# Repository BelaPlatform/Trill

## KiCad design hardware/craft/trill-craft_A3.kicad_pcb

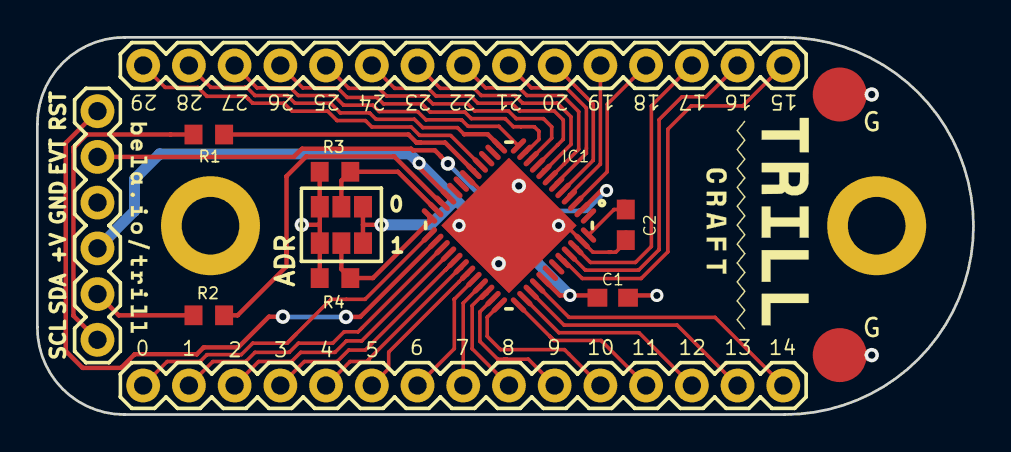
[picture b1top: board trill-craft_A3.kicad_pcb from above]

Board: 2 copper layers, 52.0 x 21.0 mm, 14 parts (0 on the bottom side), 41 nets.

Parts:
C1, C2: C-USC0603; C0603
G: Conn_01x01_Female; Circular_pad_smd
G#2: Conn_01x01_Female; Circular_pad_smd
IC1: CY8C206X6A; QFN48-LEADS
JP1: M06SILK_FEMALE_PTH; 1X06
JP3, JP4: Conn_01x15_Female; 1X15
Jumper0, Jumper1: Conn_01x03_Female; DOUBLE_SOLDER_JUMPER
R1, R2, R3, R4: R-EU_R0603; R0603

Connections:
/EVENT: IC1.2, JP1.2
/I2C_SCL: JP1.6, R1.2
/I2C_SDA: JP1.5, R2.2
/XRES: IC1.26, JP1.1
GND: C1.1, C2.2, G.1, G#2.1, IC1.18, IC1.47, IC1.EXP, JP1.3, Jumper0.3, Jumper1.3, R3.2, R4.2
unnamed: C2.1, IC1.48
unnamed: IC1.3, JP3.4
unnamed: IC1.4, JP3.5
unnamed: IC1.5, JP3.6
unnamed: IC1.6, JP3.7
unnamed: IC1.7, JP3.8
unnamed: IC1.8, JP3.9
unnamed: IC1.9, JP3.10
unnamed: IC1.10, JP3.11
unnamed: IC1.11, JP3.12
unnamed: IC1.12, JP3.13
unnamed: IC1.13, JP3.14
unnamed: IC1.16, JP3.15
unnamed: IC1.17, R1.1
unnamed: IC1.22, R2.1
unnamed: IC1.23, Jumper0.2, R3.1
unnamed: IC1.24, Jumper1.2, R4.1
unnamed: IC1.25, JP4.1
unnamed: IC1.27, JP4.2
unnamed: IC1.28, JP4.3
unnamed: IC1.29, JP4.4
unnamed: IC1.30, JP4.5
unnamed: IC1.31, JP4.6
unnamed: IC1.32, JP4.7
unnamed: IC1.33, JP4.8
unnamed: IC1.34, JP4.9
unnamed: IC1.35, JP4.10
unnamed: IC1.36, JP4.11
unnamed: IC1.37, JP4.12
unnamed: IC1.38, JP4.13
unnamed: IC1.39, JP4.14
unnamed: IC1.40, JP4.15
unnamed: IC1.44, JP3.1
unnamed: IC1.45, JP3.2
unnamed: IC1.46, JP3.3
VCC: C1.2, IC1.21, IC1.41, JP1.4, Jumper0.1, Jumper1.1

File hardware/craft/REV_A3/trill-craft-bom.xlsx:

Name | Quantity | Value | Package | Description | Mouser # | Digi-Key # | Datasheet / Notes
C1 | 1 | 0.1uF | "0603" | Capacitor ceramic 0402; standard bypass cap 5V+
C2 | 1 | 2.2nF | "0603" | Capacitor ceramic 0402; 5% | 81-GRM36X222J50
IC1 | 1 | CY8C20636A-24LTXI | 48-QFN, 7x7mm | IC Cypress SoC | 727-CY8C20636A24LTXI
R1-R2 | 2 | 100 ohm | "0603" | Resistor 0603 (standard part)
R3-R4 | 2 | 47k ohm | "0603" | Resistor 0603 (standard part)
Total | 7

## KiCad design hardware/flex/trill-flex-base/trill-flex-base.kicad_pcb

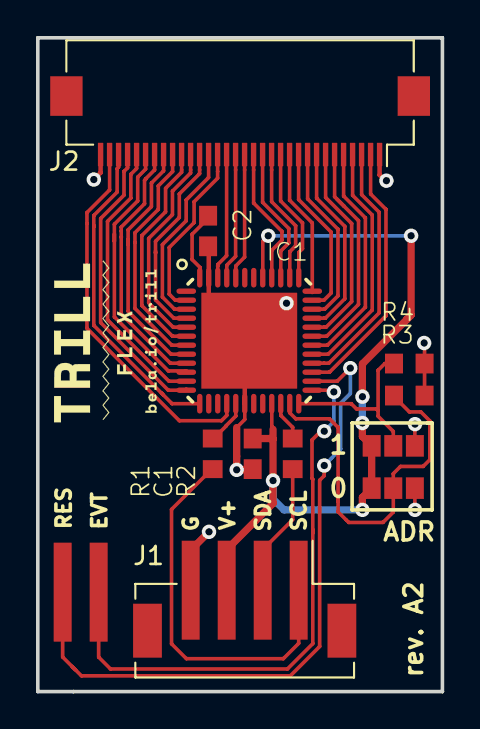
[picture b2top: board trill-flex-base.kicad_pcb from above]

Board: 2 copper layers, 22.5 x 36.3 mm, 12 parts (0 on the bottom side), 41 nets.

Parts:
C1, C2: C-USC0603; C0603
IC1: CY8C206X6A; QFN48-LEADS
J1: Conn_01x04_Female; JST_PH_B4B-PH-SM4-TB_04x2.00mm_Straight
J2: Conn_01x32; Hirose_FH12-32S-0.5SH_1x32-1MP_P0.50mm_Horizontal
J3: Conn_01x02_Female; JST_PH02x2.00mm_only_pins
Jumper0, Jumper1: Conn_01x03_Female; DOUBLE_SOLDER_JUMPER
R1, R2, R3, R4: R-EU_R0603; R0603

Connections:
/EVENT: IC1.25, J3.2
/I2C_SCL: J1.1, R1.2
/I2C_SDA: J1.2, R2.2
/SENSE1: IC1.27, J2.2
/SENSE2: IC1.28, J2.3
/SENSE3: IC1.29, J2.4
/SENSE4: IC1.30, J2.5
/SENSE5: IC1.31, J2.6
/SENSE6: IC1.32, J2.7
/SENSE7: IC1.33, J2.8
/SENSE8: IC1.34, J2.9
/SENSE9: IC1.35, J2.10
/SENSE10: IC1.36, J2.11
/SENSE11: IC1.37, J2.12
/SENSE12: IC1.38, J2.13
/SENSE13: IC1.39, J2.14
/SENSE14: IC1.40, J2.15
/SENSE15: IC1.44, J2.16
/SENSE16: IC1.45, J2.17
/SENSE17: IC1.46, J2.18
/SENSE18: IC1.2, J2.19
/SENSE19: IC1.3, J2.20
/SENSE20: IC1.4, J2.21
/SENSE21: IC1.5, J2.22
/SENSE22: IC1.6, J2.23
/SENSE23: IC1.7, J2.24
/SENSE24: IC1.8, J2.25
/SENSE25: IC1.9, J2.26
/SENSE26: IC1.10, J2.27
/SENSE27: IC1.11, J2.28
/SENSE28: IC1.12, J2.29
/SENSE29: IC1.13, J2.30
/SENSE30: IC1.16, J2.31
/XRES: IC1.26, J3.1
GND: C1.1, C2.2, IC1.18, IC1.47, IC1.EXP, J1.4, J2.1, J2.32, Jumper0.3, Jumper1.3, R3.2, R4.2
unnamed: C2.1, IC1.48
unnamed: IC1.17, R1.1
unnamed: IC1.22, R2.1
unnamed: IC1.23, Jumper0.2, R3.1
unnamed: IC1.24, Jumper1.2, R4.1
VCC: C1.2, IC1.21, IC1.41, J1.3, Jumper0.1, Jumper1.1

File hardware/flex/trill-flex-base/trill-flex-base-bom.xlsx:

Name | Quantity | Value | Package | Description | Mouser # | Digi-Key # | Datasheet / Notes
C1 | 1 | 0.1uF | "0603" | Capacitor ceramic 0402; standard bypass cap 5V+
C2 | 1 | 2.2nF | "0603" | Capacitor ceramic 0402; 5% | 81-GRM36X222J50
IC1 | 1 | CY8C20636A-24LTXI | 48-QFN, 7x7mm | IC Cypress SoC | 727-CY8C20636A24LTXI
J1 | 1 | Grove connector, vertical SMT | SMD | 4-pin 2mm vertical Grove connector (Seeed)
R1-R2 | 2 | 100 ohm | "0603" | Resistor 0603 (standard part)
R3-R4 | 2 | 47k ohm | "0603" | Resistor 0603 (standard part)
Total | 8
